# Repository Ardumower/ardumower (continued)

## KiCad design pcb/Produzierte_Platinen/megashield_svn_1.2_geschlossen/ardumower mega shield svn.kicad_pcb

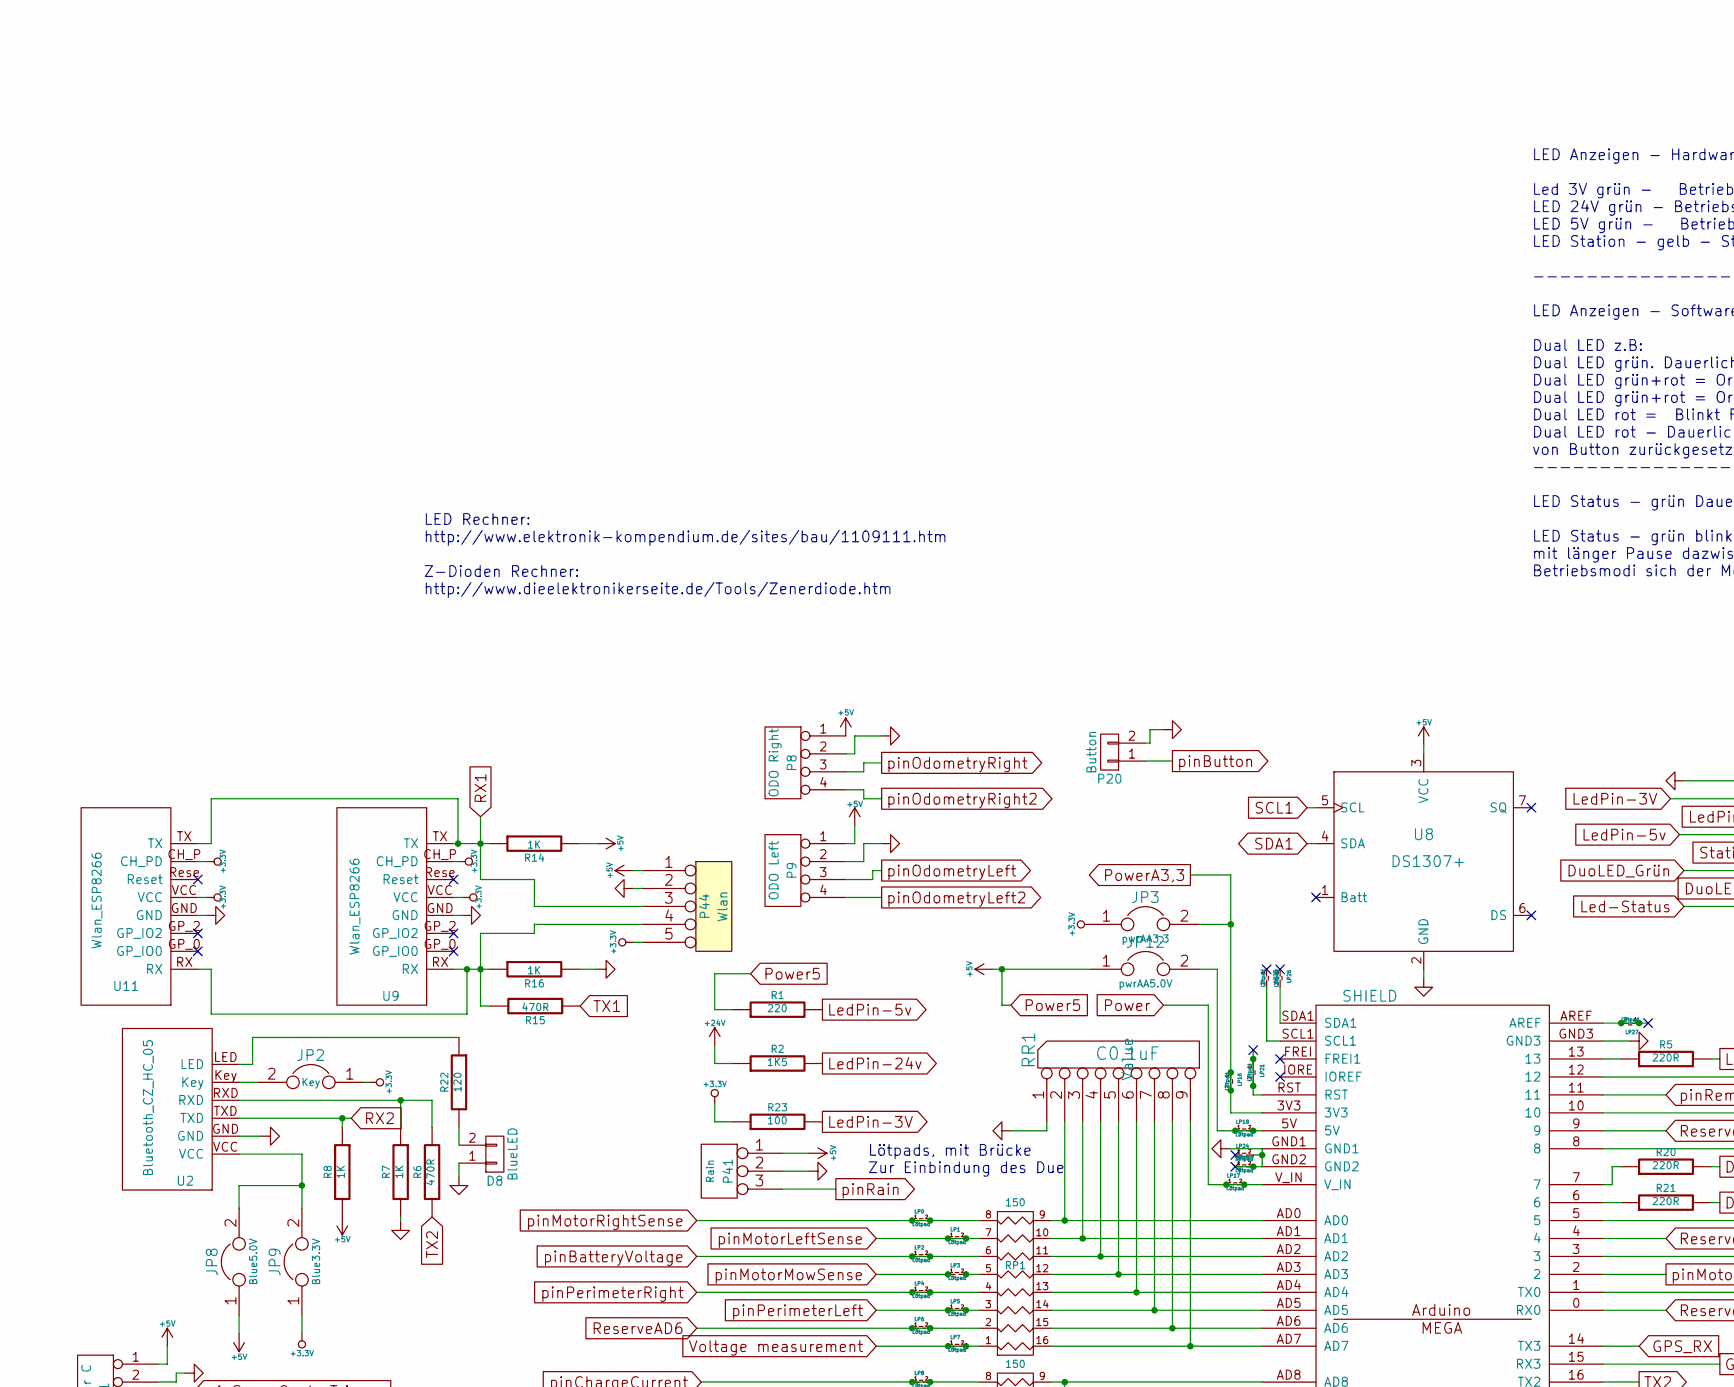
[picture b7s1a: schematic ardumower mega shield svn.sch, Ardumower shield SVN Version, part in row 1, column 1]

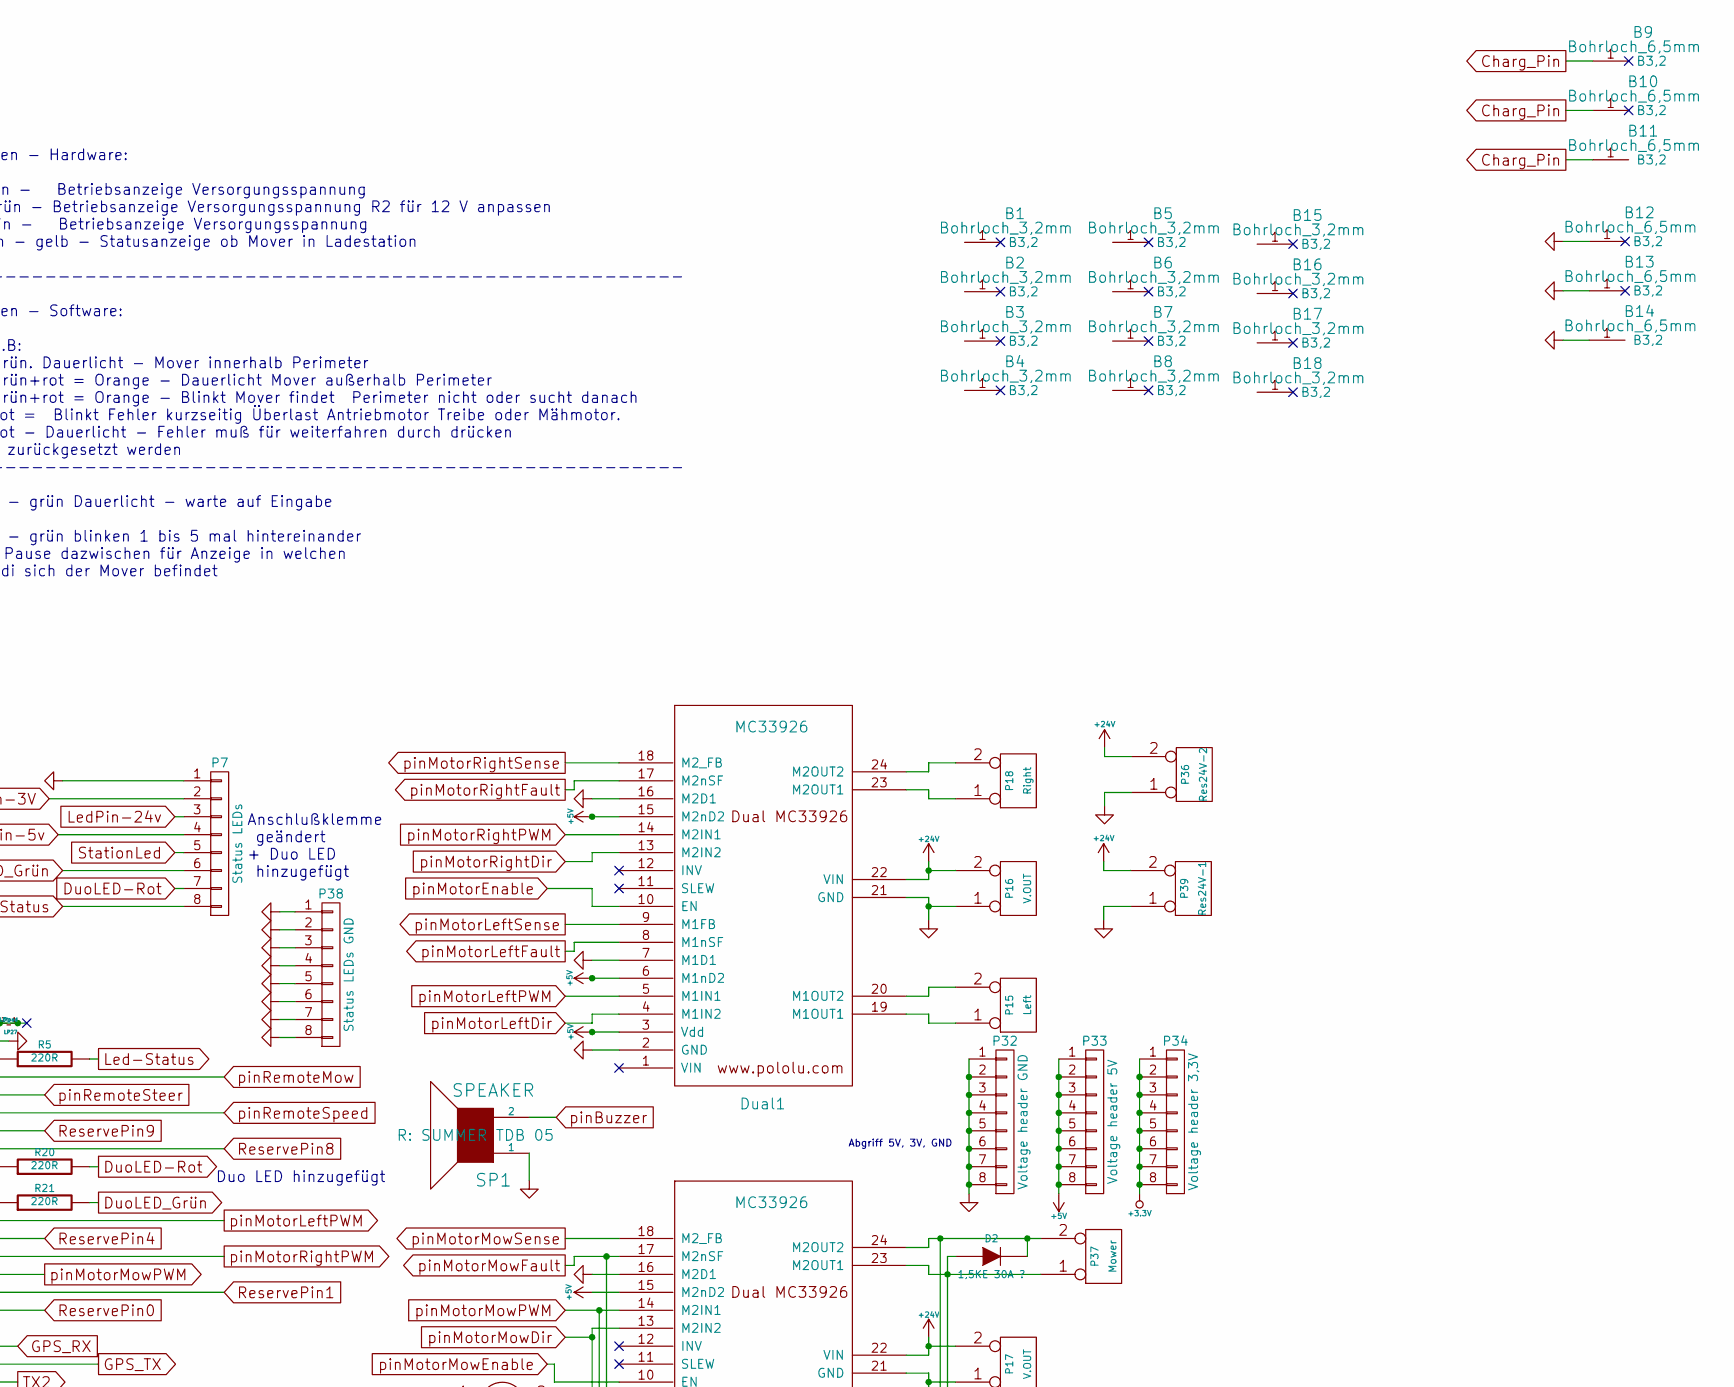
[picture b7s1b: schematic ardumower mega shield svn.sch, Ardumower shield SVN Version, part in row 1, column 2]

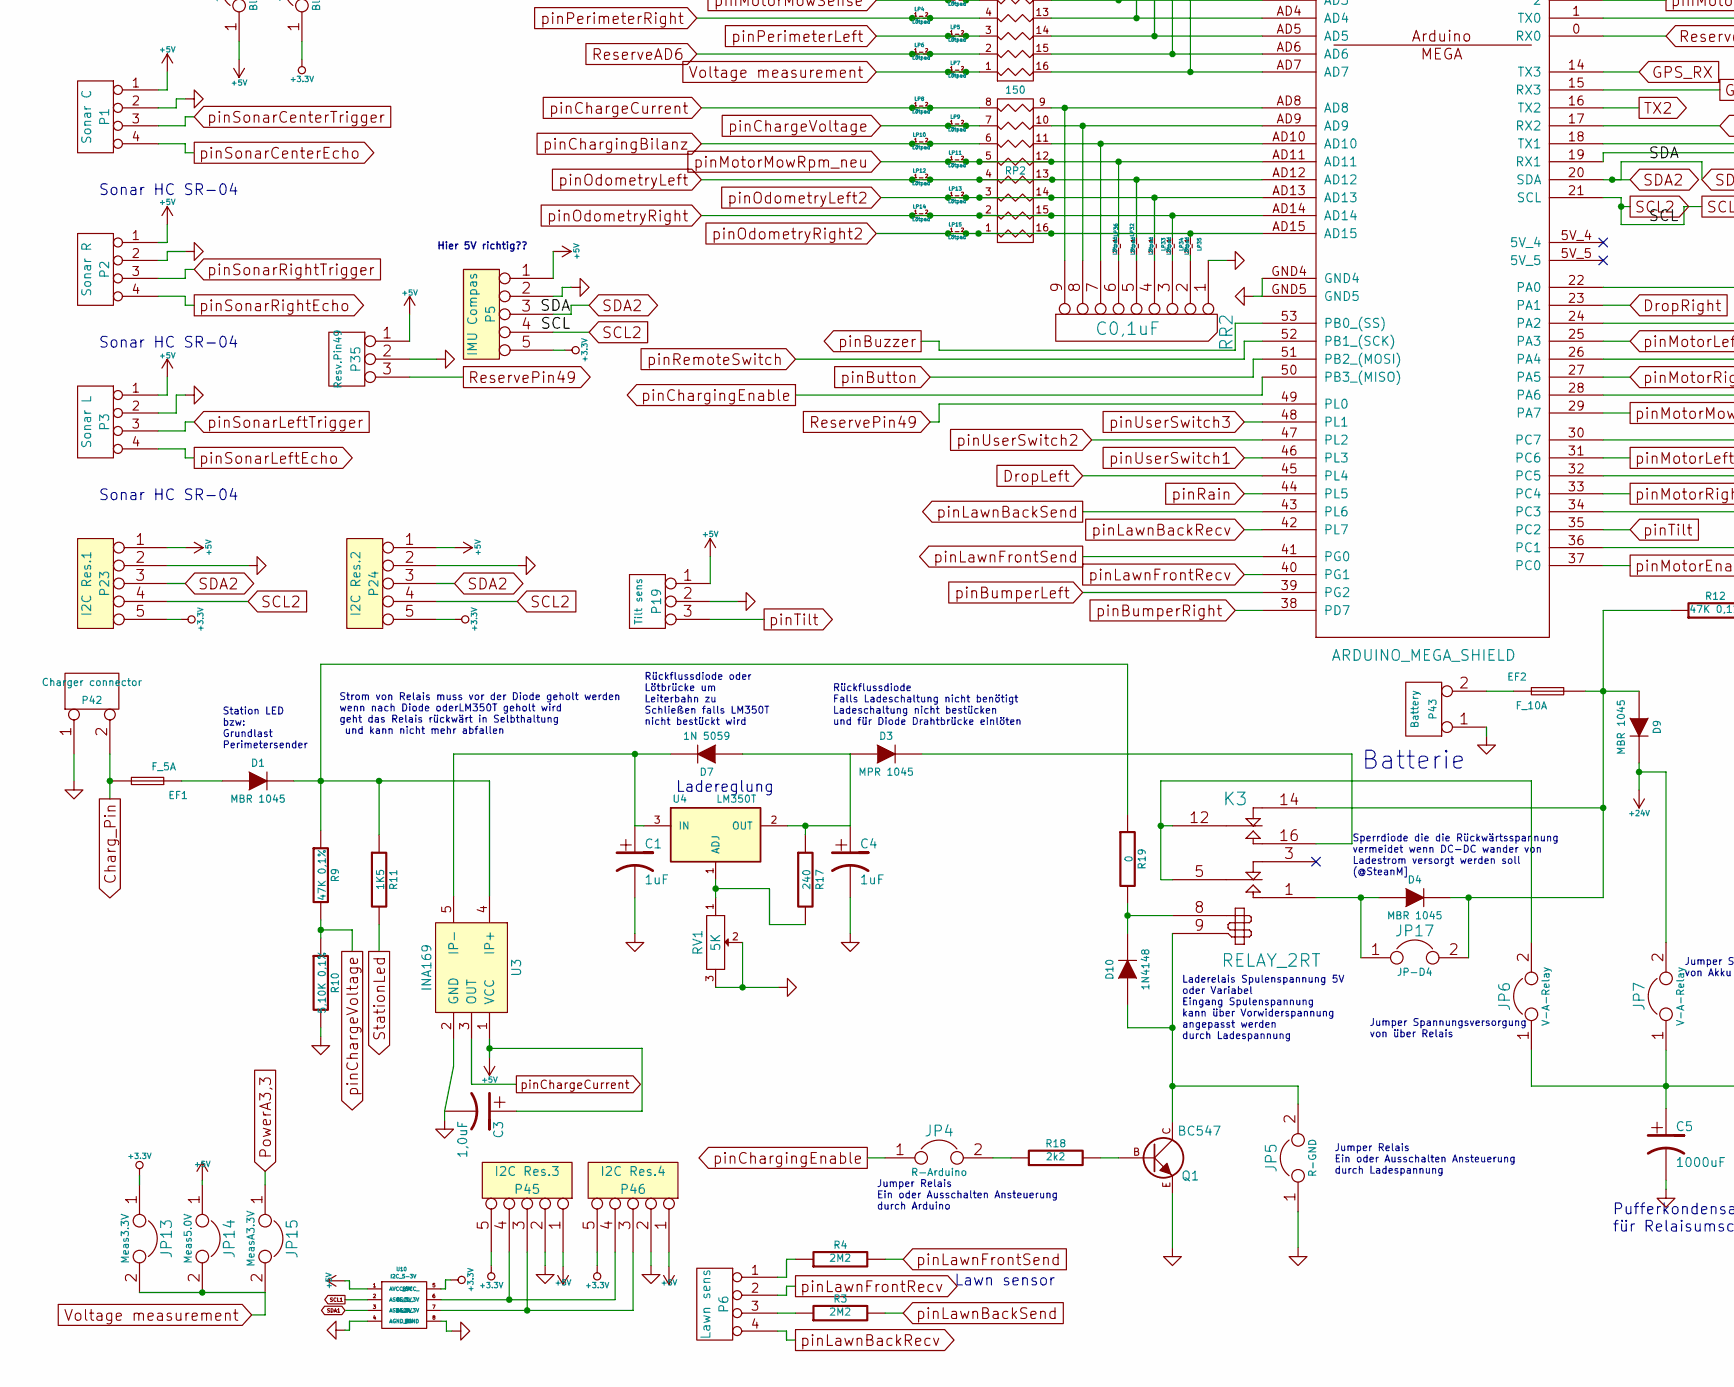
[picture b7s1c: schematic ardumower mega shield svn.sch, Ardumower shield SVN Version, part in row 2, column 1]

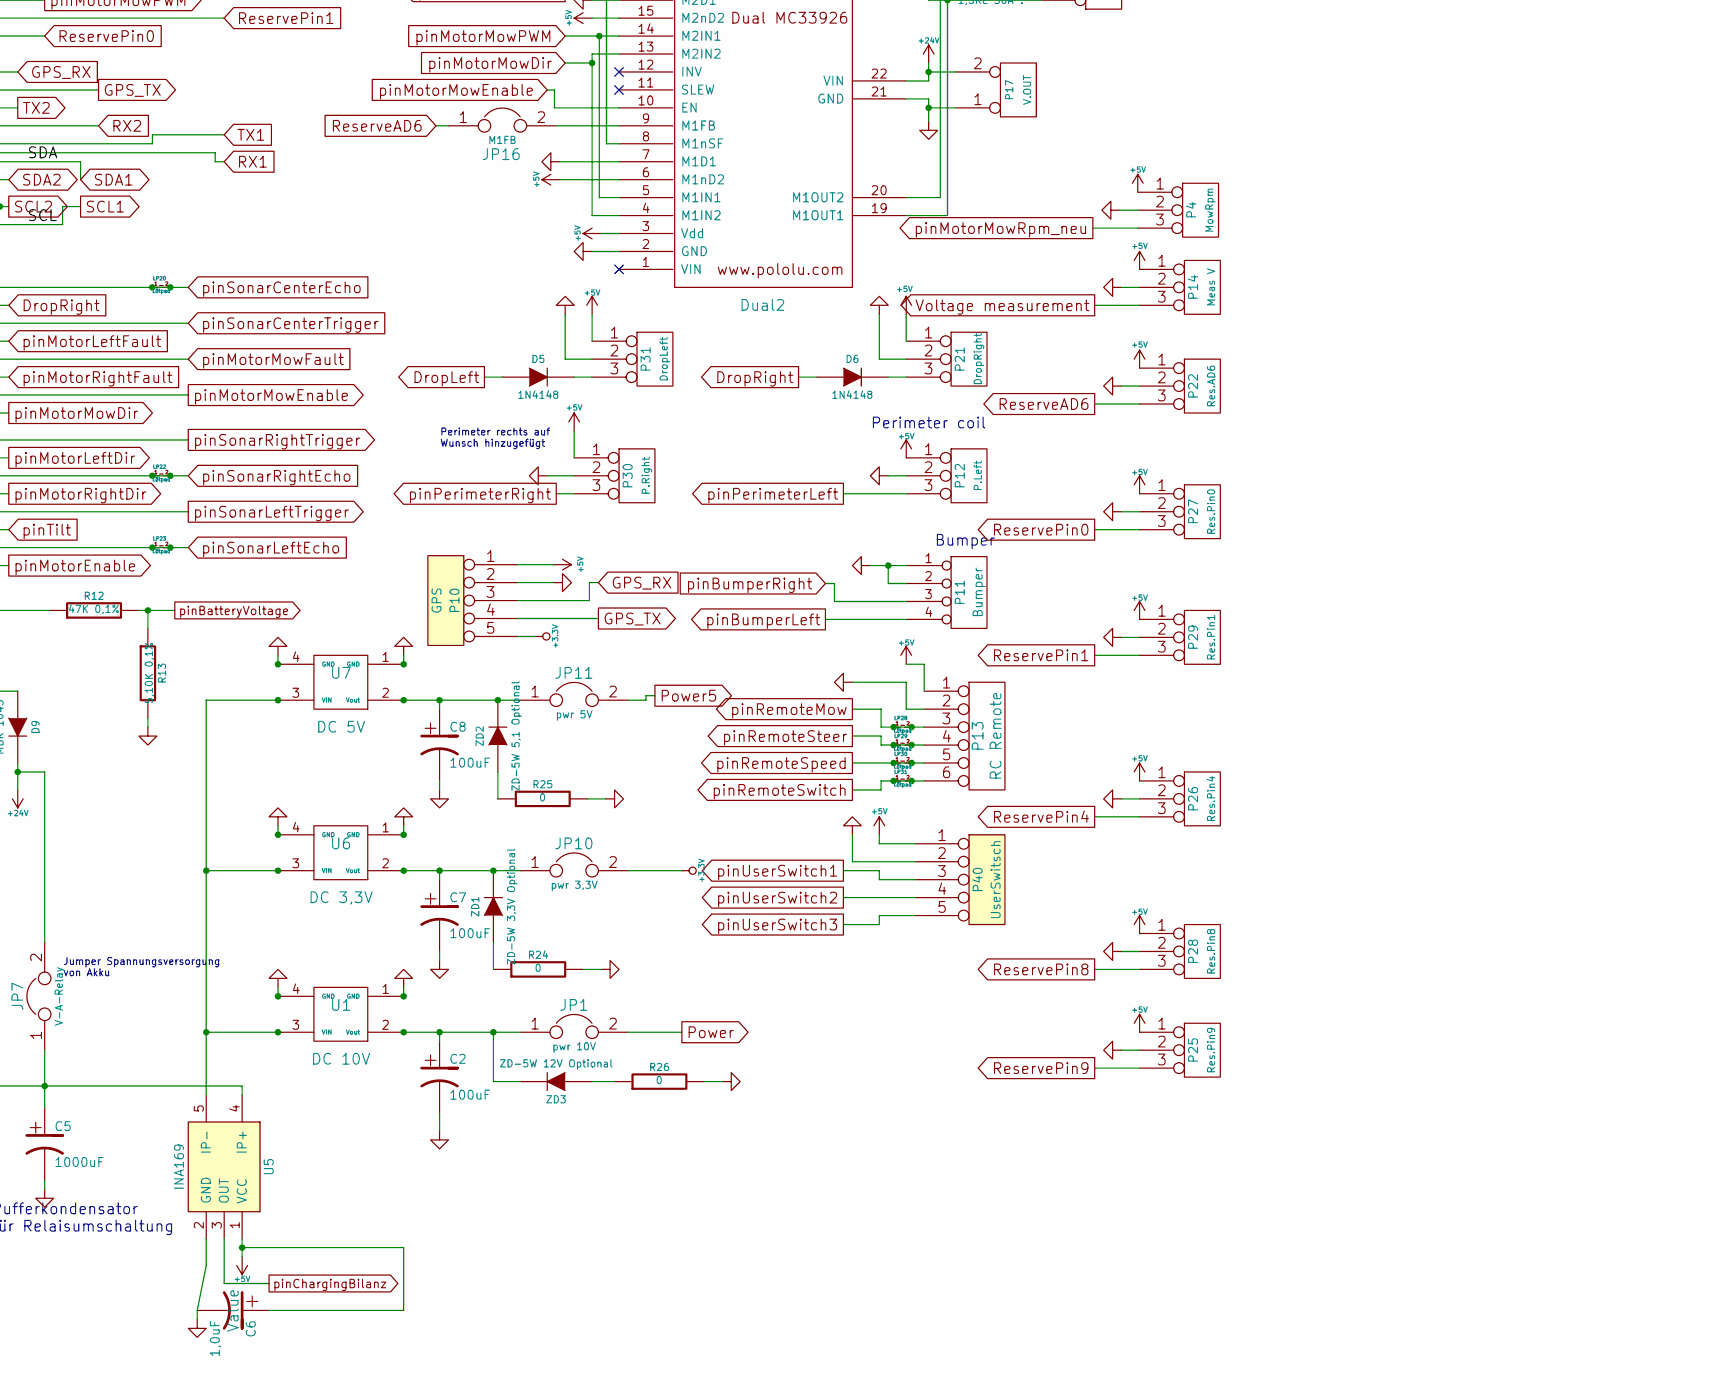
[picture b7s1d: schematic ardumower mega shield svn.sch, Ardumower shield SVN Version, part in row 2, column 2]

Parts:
B1, B2, B3, B4, B5, B6, B7, B8, B15, B16, B17, B18: Bohrloch_3,2mm
B9, B10, B11, B12, B13, B14: Bohrloch_6,5mm
C1, C4: 1uF; Elko_vert_11.2x6.3mm_RM2.5_RM5.0
C2, C7, C8: 100uF; Elko_vert_11.2x6.3mm_RM2.5_RM5.0
C3, C6: 1,0uF; Elko_vert_11.2x6.3mm_RM2.5_RM5.0
C5: 1000uF; Elko_vert_31.5x16mm_RM7.5
D1, D4: MBR 1045; MBR1045
D2: 1,5KE 30A ?; Diode_ligend_RM10
D3: MPR 1045; MBR1045
D5, D6, D10: 1N4148; Diode_ligend_RM10
D7: 1N 5059; Diode_ligend_RM10
D8: BlueLED; Diode_LED_5mm_round_vertical
D9: MBR 1045; MBR1045_liegend
Dual1, Dual2: MC33926; MC_33926_31polig_mit_Bohrloch_neue_Masse
EF1: F_5A; Fuseholder_Reichelt_PL112000
EF2: F_10A; Fuseholder_Reichelt_PL112000
JP1: pwr 10V; Pin_Header_Straight_1x02
JP2: Key; Pin_Header_Straight_1x02
JP3: pwrAA3,3; Pin_Header_Straight_1x02
JP4: R-Arduino; Pin_Header_Straight_1x02
JP5: R-GND; Pin_Header_Straight_1x02
JP6, JP7: V-A-Relay; Pin_Header_Straight_1x02
JP8: Blue5.0V; Pin_Header_Straight_1x02
JP9: Blue3.3V; Pin_Header_Straight_1x02
JP10: pwr 3,3V; Pin_Header_Straight_1x02
JP11: pwr 5V; Pin_Header_Straight_1x02
JP12: pwrAA5.0V; Pin_Header_Straight_1x02
JP13: Meas3.3V; Pin_Header_Straight_1x02
JP14: Meas5.0V; Pin_Header_Straight_1x02
JP15: MeasA3.3V; Pin_Header_Straight_1x02
JP16: M1FB; Pin_Header_Straight_1x02
JP17: JP-D4; Pin_Header_Straight_1x02
K3: RELAY_2RT; Relais_DPDT_Schrack-RT2_RM5mm_3D_Kontaktbelegung_geändert_F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
LP0, LP1, LP2, LP3, LP4, LP5, LP6, LP7, LP8, LP9, LP10, LP11, LP12, LP13, LP14, LP15, LP16, LP17, LP18, LP19, LP20, LP21, LP22, LP23, LP24, LP25, LP26, LP27, LP28, LP29, LP30, LP31: Lötpad; Lötpad_1x02
LP32, LP33, LP34, LP35, LP36: Lötpad; Lötpad0,508_CU
P1: Sonar C; Pin_Header_Straight_1x04
P2: Sonar R; Pin_Header_Straight_1x04
P3: Sonar L; Pin_Header_Straight_1x04
P4: MowRpm; Pin_Header_Straight_1x03
P5: IMU Compas; Pin_Header_Straight_1x05
P6: Lawn sens; Pin_Header_Straight_1x04
P7: Status LEDs; Pin_Header_Straight_1x08
P8: ODO Right; Pin_Header_Straight_1x04
P9: ODO Left; Pin_Header_Straight_1x04
P10: GPS; Pin_Header_Straight_1x05
P11: Bumper; Pin_Header_Straight_1x04
P12: P.Left; Pin_Header_Straight_1x03
P13: RC Remote; Pin_Header_Straight_1x06
P14: Meas V; Pin_Header_Straight_1x03
P15: Left; Anschlussklemme_2P_RM5,08
P16, P17: V.OUT; Anschlussklemme_2P_RM5,08
P18: Right; Anschlussklemme_2P_RM5,08
P19: Tilt sens; Pin_Header_Straight_1x03
P20: Button; Pin_Header_Straight_1x02
P21: DropRight; Pin_Header_Straight_1x03
P22: Res.AD6; Pin_Header_Straight_1x03
P23: I2C Res.1; Pin_Header_Straight_1x05
P24: I2C Res.2; Pin_Header_Straight_1x05
P25: Res.Pin9; Pin_Header_Straight_1x03
P26: Res.Pin4; Pin_Header_Straight_1x03
P27: Res.Pin0; Pin_Header_Straight_1x03
P28: Res.Pin8; Pin_Header_Straight_1x03
P29: Res.Pin1; Pin_Header_Straight_1x03
P30: P.Right; Pin_Header_Straight_1x03
P31: DropLeft; Pin_Header_Straight_1x03
P32: Voltage header GND; Pin_Header_Straight_1x08
P33: Voltage header 5V; Pin_Header_Straight_1x08
P34: Voltage header 3,3V; Pin_Header_Straight_1x08
P35: Resv.Pin49; Pin_Header_Straight_1x03
P36: Res24V-2; Anschlussklemme_2P_RM5,08
P37: Mower; Anschlussklemme_RM5,08-RM7,62
P38: Status LEDs GND; Pin_Header_Straight_1x08
P39: Res24V-1; Anschlussklemme_2P_RM5,08
P40: UserSwitsch; Pin_Header_Straight_1x05
P41: Rain; Pin_Header_Straight_1x03
P42: Charger connector; Anschlussklemme_RM5,08-RM7,62
P43: Battery; Anschlussklemme_RM5,08-RM7,62
P44: Wlan; Pin_Header_Straight_1x05
P45: I2C Res.3; Pin_Header_Straight_1x05
P46: I2C Res.4; Pin_Header_Straight_1x05
Q1: BC547; TO92-EBC
R1: 220; Resistor_Horizontal_RM15mm
R2, R11: 1K5; Resistor_Horizontal_RM10mm
R3, R4: 2M2; Resistor_Horizontal_RM10mm
R5, R20, R21: 220R; Resistor_Horizontal_RM15mm
R6, R15: 470R; Resistor_Horizontal_RM15mm
R7, R8, R14, R16: 1K; Resistor_Horizontal_RM15mm
R9: 47K 0,1%; Resistor_Horizontal_RM10mm
R10: 5,10K 0,1%; Resistor_Horizontal_RM10mm
R12: 47K 0,1%; Resistor_Horizontal_RM15mm
R13: 5,10K 0,1%; Resistor_Horizontal_RM15mm
R17: 240; Resistor_Horizontal_RM15mm
R18: 2k2; Resistor_Horizontal_RM10mm
R19: 0; Resistor_Horizontal_RM10mm
R22: 120; Resistor_Horizontal_RM15mm
R23: 100; Resistor_Horizontal_RM15mm
R24, R25, R26: 0; Resistor_Horizontal_RM15mm
RP1, RP2: 150; DIP-16__300
RR1, RR2: C0,1uF; Kondensatorenleiste_8er_9pin_3D
RV1: 5K; Potentiometer_VishaySpectrol-Econtrim-Type36T_3D
SHIELD1: ARDUINO_MEGA_SHIELD; ARDUINO_MEGA_SHIELD_DUO_3D
SP1: SPEAKER; Buzzer_12x9.5RM7.6_RM5.0
U1: DC 10V; DC_DC_DSN2596_mit_Bohrloch_doppelte_Lochreihe
U2: Bluetooth_CZ_HC_05; Bluetooth_Buchse_Platz
U3, U5: INA169
U4: LM350T; LM350T_3D_muss_noch_auf_Masse_geprüft_werden
U6: DC 3,3V; DC_DC_DSN2596_mit_Bohrloch_doppelte_Lochreihe
U7: DC 5V; DC_DC_DSN2596_mit_Bohrloch_doppelte_Lochreihe
U8: DS1307+; Tiny_RTC_DS1307_geändert_mit_Bohrloch_4Lochreihen
U9, U11: Wlan_ESP8266; Wlan_ESP8266_3D
U10: I2C_5-3V
ZD1: ZD-5W 3,3V Optional; Diode_ligend_RM10
ZD2: ZD-5W 5,1 Optional; Diode_ligend_RM10
ZD3: ZD-5W 12V Optional; Diode_ligend_RM10

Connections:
+3.3V: JP2.1, JP3.1, JP9.1, JP10.2, JP13.1, P5.5, P10.5, P23.5, P24.5, P34.1, P34.2, P34.3, P34.4, P34.5, P34.6, P34.7, P34.8, P44.5, P45.5, P46.5, R23.1, U9.CH_P (CH_PD), U9.VCC, U10.5 (BVCC_), U11.CH_P (CH_PD), U11.VCC
+24V: D9.2 (K), Dual1.22 (VIN), Dual2.22 (VIN), JP7.2, P16.2 (PM), P17.2 (PM), P36.2 (PM), P39.2 (PM), R2.1
Charg_Pin: B9.1, B10.1, B11.1, EF1.1, P42.2 (PM)
DropLeft: D5.1 (A), SHIELD1.45 (PL4)
DropRight: D6.1 (A), SHIELD1.23 (PA1)
DuoLED-Rot: P7.7, R20.2
DuoLED_Grün: P7.6, R21.2
GND: B12.1, B13.1, B14.1, C1.2, C2.2, C3.2, C4.2, C5.2, C6.2, C7.2, C8.2, D8.1, Dual1.2 (GND), Dual1.7 (M1D1), Dual1.16 (M2D1), Dual1.21 (GND), Dual2.2 (GND), Dual2.7 (M1D1), Dual2.16 (M2D1), Dual2.21 (GND), JP5.1, LP19.1, LP19.2, LP24.1, LP24.2, P1.2, P2.2, P3.2, P4.2 (PM), P5.2, P7.1, P8.2, P9.2, P10.2, P11.1, P11.2, P12.2 (PM), P13.2, P14.2 (PM), P16.1, P17.1, P19.2 (PM), P20.2, P21.2 (PM), P22.2 (PM), P23.2, P24.2, P25.2 (PM), P26.2 (PM), P27.2 (PM), P28.2 (PM), P29.2 (PM), P30.2 (PM), P31.2 (PM), P32.1, P32.2, P32.3, P32.4, P32.5, P32.6, P32.7, P32.8, P35.2 (PM), P36.1, P38.1, P38.2, P38.3, P38.4, P38.5, P38.6, P38.7, P38.8, P39.1, P40.2, P41.2 (PM), P42.1, P43.1, P44.2, P45.2, P46.2, Q1.E, R7.2, R10.2, R13.2, R16.2, R24.2, R25.2, R26.2, RR1.1 (COM), RR2.1 (COM), RV1.2, RV1.3, SHIELD1.GND1, SHIELD1.GND2, SHIELD1.GND3, SHIELD1.GND4, SHIELD1.GND5, SP1.1, U1.1 (GND), U1.4 (GND), U2.GND, U3.2 (GND), U5.2 (GND), U6.1 (GND), U6.4 (GND), U7.1 (GND), U7.4 (GND), U8.2 (GND), U9.GND, U10.4 (AGND_5V), U10.8 (BGND), U11.GND
GPS_RX: P10.3, SHIELD1.14 (TX3)
GPS_TX: P10.4, SHIELD1.15 (RX3)
Led-Status: P7.8, R5.2
LedPin-3V: P7.2, R23.2
LedPin-5v: P7.4, R1.2
LedPin-24v: P7.3, R2.2
unnamed: C1.1, D7.2 (K), U3.5 (IP-), U4.3 (IN)
unnamed: C2.1, JP1.1, U1.2 (Vout), ZD3.2 (K)
unnamed: C4.1, D3.1 (A), D7.1 (A), R17.1, U4.2 (OUT)
unnamed: C5.1, JP6.1, JP7.1, U5.4 (IP+)
unnamed: C7.1, JP10.1, U6.2 (Vout), ZD1.2 (K)
unnamed: C8.1, JP11.1, U7.2 (Vout), ZD2.2 (K)
unnamed: D1.1 (A), EF1.2
unnamed: D1.2 (K), R9.1, R11.1, R19.1, U3.4 (IP+)
unnamed: D2.1 (A), Dual2.19 (M1OUT1), Dual2.23 (M2OUT1), P37.1
unnamed: D2.2 (K), Dual2.20 (M1OUT2), Dual2.24 (M2OUT2), P37.2 (PM)
unnamed: D3.2 (K), K3.16 (T2)
unnamed: D4.1 (A), JP17.1, K3.1 (T1)
unnamed: D4.2 (K), D9.1 (A), EF2.1, JP17.2, K3.14 (R2), R12.1
unnamed: D5.2 (K), P31.3
unnamed: D6.2 (K), P21.3
unnamed: D8.2, R22.2
unnamed: D10.1 (A), JP5.2, K3.9, Q1.C
unnamed: D10.2 (K), K3.8, R19.2
unnamed: Dual1.19 (M1OUT1), P15.1
unnamed: Dual1.20 (M1OUT2), P15.2 (PM)
unnamed: Dual1.23 (M2OUT1), P18.1
unnamed: Dual1.24 (M2OUT2), P18.2 (PM)
unnamed: Dual2.9 (M1FB), JP16.2
unnamed: EF2.2, P43.2 (PM)
unnamed: JP2.2, U2.Key
unnamed: JP4.2, R18.1
unnamed: JP6.2, K3.5 (C1), K3.12 (C2)
unnamed: JP8.2, JP9.2, U2.VCC
unnamed: JP12.2, LP18.1, LP18.2, SHIELD1.5V
unnamed: LP3.2, RP1.5
unnamed: LP21.1, LP21.2, SHIELD1.RST
unnamed: LP25.2, SHIELD1.SCL1
unnamed: LP26.2, SHIELD1.SDA1
unnamed: LP27.1, LP27.2, SHIELD1.AREF
unnamed: LP32.2, RR2.5
unnamed: LP33.2, RR2.4
unnamed: LP34.2, RR2.3
unnamed: LP35.2, RR2.2
unnamed: LP36.2, RR2.6
unnamed: P6.1, R4.1
unnamed: P6.3, R3.1
unnamed: P44.4, R15.2, R16.1, U9.RX, U11.RX
unnamed: P45.3, P46.3, U10.7 (BSDA_3V)
unnamed: P45.4, P46.4, U10.6 (BSCL_3V)
unnamed: Q1.B, R18.2
unnamed: R5.1, SHIELD1.13
unnamed: R6.2, R7.1, U2.RXD
unnamed: R17.2, RV1.1, U4.1 (ADJ)
unnamed: R20.1, SHIELD1.7
unnamed: R21.1, SHIELD1.6
unnamed: R22.1, U2.LED
unnamed: R24.1, ZD1.1 (A)
unnamed: R25.1, ZD2.1 (A)
unnamed: R26.1, ZD3.1 (A)
unnamed: RP1.9 (R8), RR1.2, SHIELD1.AD0
unnamed: RP1.10 (R7), RR1.3, SHIELD1.AD1
unnamed: RP1.11 (R6), RR1.4, SHIELD1.AD2
unnamed: RP1.12 (R5), RR1.5, SHIELD1.AD3
unnamed: RP1.13 (R4), RR1.6, SHIELD1.AD4
unnamed: RP1.14 (R3), RR1.7, SHIELD1.AD5
unnamed: RP1.15 (R2), RR1.8, SHIELD1.AD6
unnamed: RP1.16 (R1), RR1.9, SHIELD1.AD7
unnamed: RP2.9 (R8), RR2.9, SHIELD1.AD8
unnamed: RP2.10 (R7), RR2.8, SHIELD1.AD9
unnamed: RP2.11 (R6), RR2.7, SHIELD1.AD10
unnamed: U1.3 (VIN), U5.5 (IP-), U6.3 (VIN), U7.3 (VIN)
Power: JP1.2, LP17.1, LP17.2, SHIELD1.V_IN
Power5: C3.1, C6.1, Dual1.3 (Vdd), Dual1.6 (M1nD2), Dual1.15 (M2nD2), Dual2.3 (Vdd), Dual2.6 (M1nD2), Dual2.15 (M2nD2), JP8.1, JP11.2, JP12.1, JP14.1, P1.1, P2.1, P3.1, P4.1, P5.1, P8.1, P9.1, P10.1, P12.1, P13.1, P14.1, P19.1, P21.1, P22.1, P23.1, P24.1, P25.1, P26.1, P27.1, P28.1, P29.1, P30.1, P31.1, P33.1, P33.2, P33.3, P33.4, P33.5, P33.6, P33.7, P33.8, P35.1, P40.1, P41.1, P44.1, P45.1, P46.1, R1.1, R8.2, R14.2, U3.1 (VCC), U5.1 (VCC), U8.3 (VCC), U10.1 (AVCC_5V)
PowerA3,3: JP3.2, JP15.1, LP16.1, LP16.2, SHIELD1.3V3
RX1: P44.3, R14.1, SHIELD1.19 (RX1), U9.TX, U11.TX
RX2: R8.1, SHIELD1.17 (RX2), U2.TXD
ReserveAD6: JP16.1, LP6.1, LP6.2, P22.3, RP1.2
ReservePin0: P27.3, SHIELD1.0 (RX0)
ReservePin1: P29.3, SHIELD1.1 (TX0)
ReservePin4: P26.3, SHIELD1.4
ReservePin8: P28.3, SHIELD1.8
ReservePin9: P25.3, SHIELD1.9
ReservePin49: P35.3, SHIELD1.49 (PL0)
SCL2: P5.4, P23.4, P24.4, SHIELD1.21 (SCL), U8.5 (SCL), U10.2 (ASCL_5V)
SDA2: P5.3, P23.3, P24.3, SHIELD1.20 (SDA), U8.4 (SDA), U10.3 (ASDA_5V)
StationLed: P7.5, R11.2
TX1: R15.1, SHIELD1.18 (TX1)
TX2: R6.1, SHIELD1.16 (TX2)
Voltage measurement: JP13.2, JP14.2, JP15.2, LP7.1, LP7.2, P14.3, RP1.1
pinBatteryVoltage: LP2.1, LP2.2, R12.2, R13.1, RP1.6
pinBumperLeft: P11.4, SHIELD1.39 (PG2)
pinBumperRight: P11.3, SHIELD1.38 (PD7)
pinButton: P20.1, SHIELD1.51 (PB2_(MOSI))
pinBuzzer: SHIELD1.53 (PB0_(SS)), SP1.2
pinChargeCurrent: LP8.1, LP8.2, RP2.8, U3.3 (OUT)
pinChargeVoltage: LP9.1, LP9.2, R9.2, R10.1, RP2.7
pinChargingBilanz: LP10.1, LP10.2, RP2.6, U5.3 (OUT)
pinChargingEnable: JP4.1, SHIELD1.50 (PB3_(MISO))
pinLawnBackRecv: P6.4, SHIELD1.42 (PL7)
pinLawnBackSend: R3.2, SHIELD1.43 (PL6)
pinLawnFrontRecv: P6.2, SHIELD1.40 (PG1)
pinLawnFrontSend: R4.2, SHIELD1.41 (PG0)
pinMotorEnable: Dual1.10 (EN), SHIELD1.37 (PC0)
pinMotorLeftDir: Dual1.4 (M1IN2), SHIELD1.31 (PC6)
pinMotorLeftFault: Dual1.8 (M1nSF), SHIELD1.25 (PA3)
pinMotorLeftPWM: Dual1.5 (M1IN1), SHIELD1.5
pinMotorLeftSense: Dual1.9 (M1FB), LP1.1, LP1.2, RP1.7
pinMotorMowDir: Dual2.4 (M1IN2), Dual2.13 (M2IN2), SHIELD1.29 (PA7)
pinMotorMowEnable: Dual2.10 (EN), SHIELD1.28 (PA6)
pinMotorMowFault: Dual2.8 (M1nSF), Dual2.17 (M2nSF), SHIELD1.26 (PA4)
pinMotorMowPWM: Dual2.5 (M1IN1), Dual2.14 (M2IN1), SHIELD1.2
pinMotorMowRpm_neu: LP11.1, LP11.2, LP36.1, P4.3, RP2.5, RP2.12 (R5), SHIELD1.AD11
pinMotorMowSense: Dual2.18 (M2_FB), LP3.1
pinMotorRightDir: Dual1.13 (M2IN2), SHIELD1.33 (PC4)
pinMotorRightFault: Dual1.17 (M2nSF), SHIELD1.27 (PA5)
pinMotorRightPWM: Dual1.14 (M2IN1), SHIELD1.3
pinMotorRightSense: Dual1.18 (M2_FB), LP0.1, LP0.2, RP1.8
pinOdometryLeft: LP12.1, LP12.2, LP32.1, P9.3, RP2.4, RP2.13 (R4), SHIELD1.AD12
pinOdometryLeft2: LP13.1, LP13.2, LP33.1, P9.4, RP2.3, RP2.14 (R3), SHIELD1.AD13
pinOdometryRight: LP14.1, LP14.2, LP34.1, P8.3, RP2.2, RP2.15 (R2), SHIELD1.AD14
pinOdometryRight2: LP15.1, LP15.2, LP35.1, P8.4, RP2.1, RP2.16 (R1), SHIELD1.AD15
pinPerimeterLeft: LP5.1, LP5.2, P12.3, RP1.3
pinPerimeterRight: LP4.1, LP4.2, P30.3, RP1.4
pinRain: P41.3, SHIELD1.44 (PL5)
pinRemoteMow: LP28.1, LP28.2, P13.3, SHIELD1.12
pinRemoteSpeed: LP30.1, LP30.2, P13.5, SHIELD1.10
pinRemoteSteer: LP29.1, LP29.2, P13.4, SHIELD1.11
pinRemoteSwitch: LP31.1, LP31.2, P13.6, SHIELD1.52 (PB1_(SCK))
pinSonarCenterEcho: LP20.1, LP20.2, P1.4, SHIELD1.22 (PA0)
pinSonarCenterTrigger: P1.3, SHIELD1.24 (PA2)
pinSonarLeftEcho: LP23.1, LP23.2, P3.4, SHIELD1.36 (PC1)
pinSonarLeftTrigger: P3.3, SHIELD1.34 (PC3)
pinSonarRightEcho: LP22.1, LP22.2, P2.4, SHIELD1.32 (PC5)
pinSonarRightTrigger: P2.3, SHIELD1.30 (PC7)
pinTilt: P19.3, SHIELD1.35 (PC2)
pinUserSwitch1: P40.3, SHIELD1.46 (PL3)
pinUserSwitch2: P40.4, SHIELD1.47 (PL2)
pinUserSwitch3: P40.5, SHIELD1.48 (PL1)

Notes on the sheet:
Sonar HC SR-04
Perimeter coil
Lawn sensor
Bumper
Batterie
Pufferkondensator für Relaisumschaltung
Jumper Spannungsversorgung von Akku
Jumper Spannungsversorgung von über Relais
Jumper Relais Ein oder Ausschalten Ansteuerung durch Arduino
Jumper Relais Ein oder Ausschalten Ansteuerung durch Ladespannung
Laderelais Spulenspannung 5V oder Variabel Eingang Spulenspannung kann über Vorwiderspannung angepasst werden durch Ladespannung
Rückflussdiode Falls Ladeschaltung nicht benötigt Ladeschaltung nicht bestücken und für Diode Drahtbrücke einlöten
Anschlußklemme geändert + Duo LED hinzugefügt
Duo LED hinzugefügt
Station LED bzw: Grundlast Perimetersender
Strom von Relais muss vor der Diode geholt werden wenn nach Diode oderLM350T geholt wird geht das Relais rückwärt in Selbthaltung und kann nicht mehr abfallen
Hier 5V richtig??
Sperrdiode die die Rückwärtsspannung vermeidet wenn DC-DC wander von Ladestrom versorgt werden soll (@SteanM]
Rückflussdiode oder Lötbrücke um Leiterbahn zu Schließen falls LM350T nicht bestückt wird
Perimeter rechts auf Wunsch hinzugefügt
Abgriff 5V, 3V, GND
LED Anzeigen - Hardware: Led 3V grün - Betriebsanzeige Versorgungsspannung LED 24V grün - Betriebsanzeige Versorgungsspannung R2 für 12 V anpassen LED 5V grün - Betriebsanzeige Versorgungsspannung LED Station - gelb - Statusanzeige ob Mover in Ladestation -------------------------------------------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
LED Rechner: http://www.elektronik-kompendium.de/sites/bau/1109111.htm Z-Dioden Rechner: http://www.dieelektronikerseite.de/Tools/Zenerdiode.htm
Ladereglung
Lötpads, mit Brücke Zur Einbindung des Due

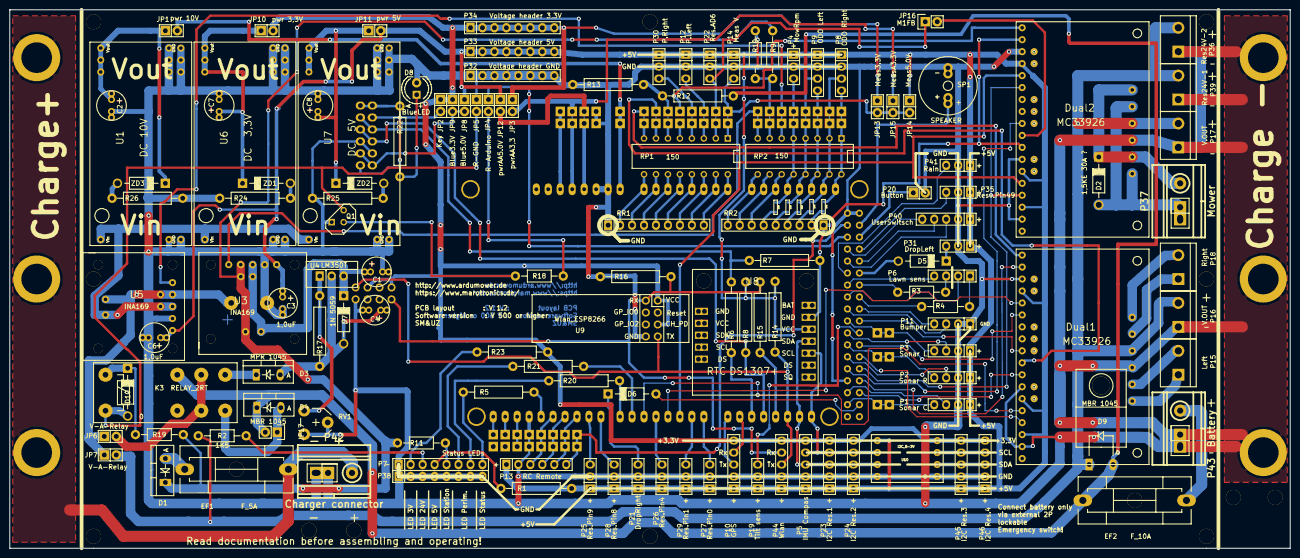
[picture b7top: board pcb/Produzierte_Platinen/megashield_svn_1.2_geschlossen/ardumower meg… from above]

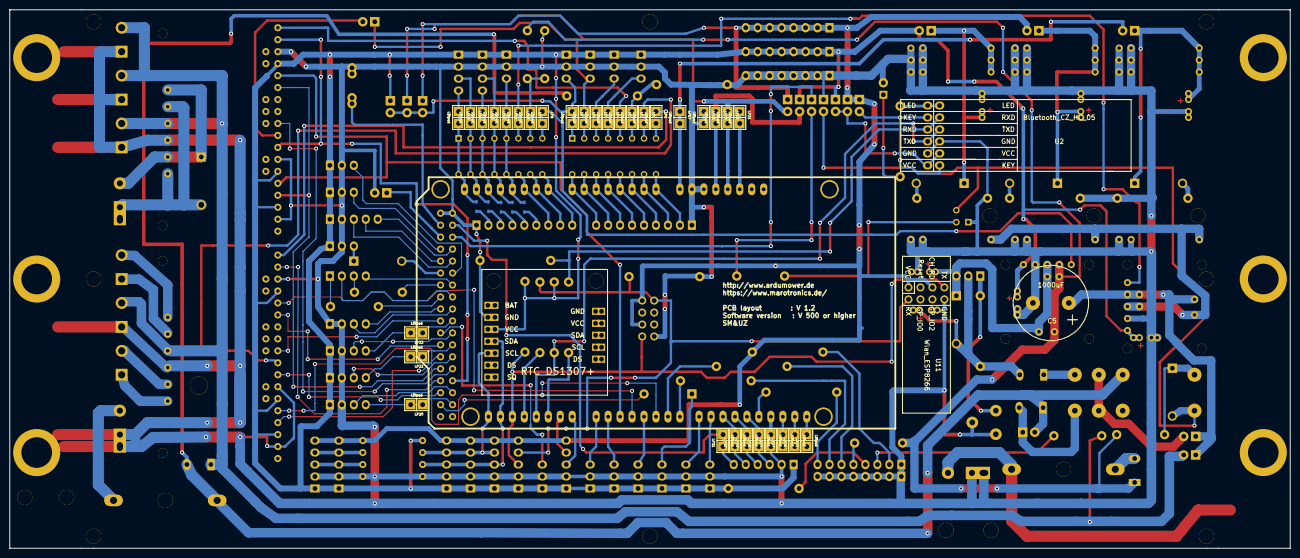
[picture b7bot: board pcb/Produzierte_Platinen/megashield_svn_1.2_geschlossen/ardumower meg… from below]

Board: 2 copper layers, 271.8 x 114.3 mm, 189 parts (36 on the bottom side), 147 nets.

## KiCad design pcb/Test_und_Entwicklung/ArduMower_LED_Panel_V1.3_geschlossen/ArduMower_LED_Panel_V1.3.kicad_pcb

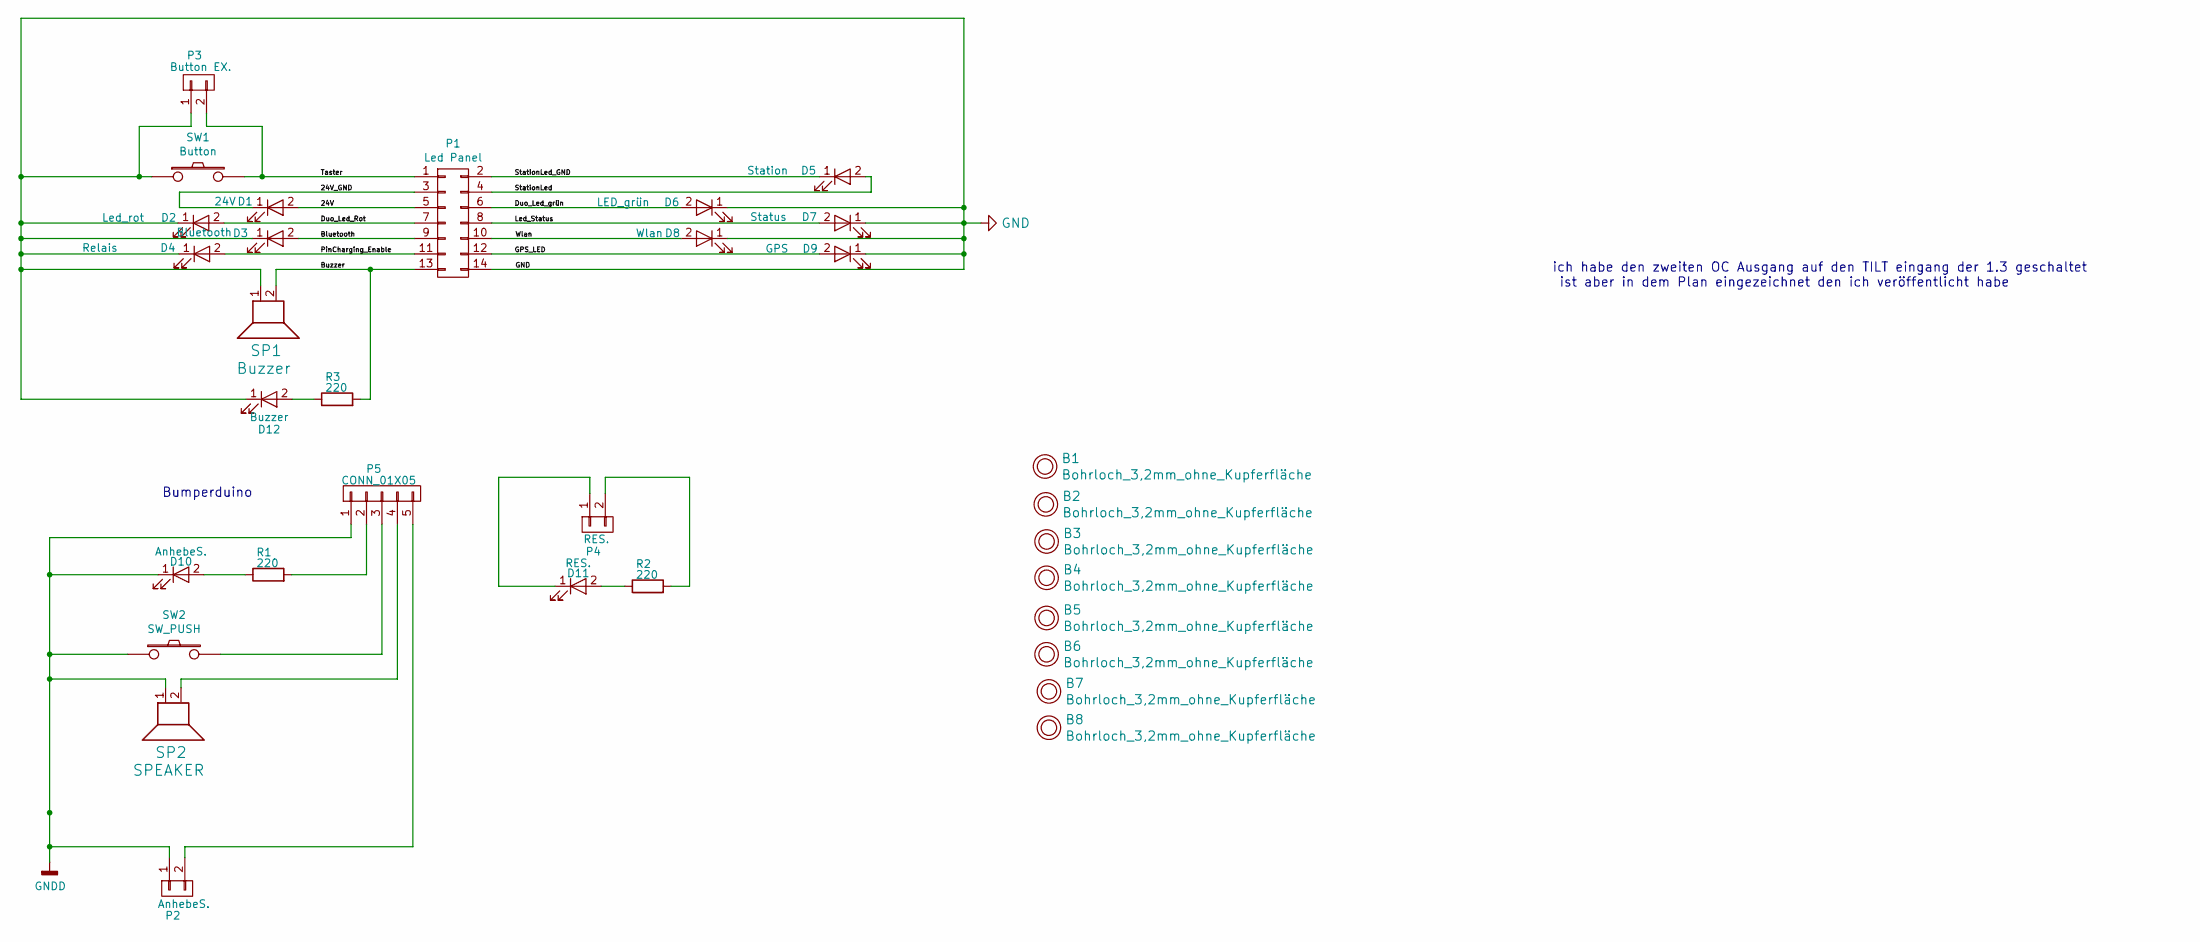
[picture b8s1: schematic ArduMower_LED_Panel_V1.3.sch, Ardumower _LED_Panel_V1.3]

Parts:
B1, B2, B3, B4, B5, B6, B7, B8: Bohrloch_3,2mm_ohne_Kupferfläche; Bohrloch_3,2mm
D1: 24V; LED_D5.0mm
D2: Led_rot; LED_D5.0mm
D3: Bluetooth; LED_D5.0mm
D4: Relais; LED_D5.0mm
D5: Station; LED_D5.0mm
D6: LED_grün; LED_D5.0mm
D7: Status; LED_D5.0mm
D8: Wlan; LED_D5.0mm
D9: GPS; LED_D5.0mm
D10: AnhebeS.; LED_D5.0mm
D11: RES.; LED_D5.0mm
D12: Buzzer; LED_D5.0mm
P1: Led Panel; Pin_Header_Angled_2x07_Pitch2.54mm
P2: AnhebeS.; Pin_Header_Angled_1x02_Pitch2.54mm
P3: Button EX.; Pin_Header_Angled_1x02_Pitch2.54mm
P4: RES.; Pin_Header_Angled_1x02_Pitch2.54mm
P5: CONN_01X05; JST_XH_S05B-XH-A_05x2.50mm_Angled
R1, R2, R3: 220; R_Axial_DIN0207_L6.3mm_D2.5mm_P10.16mm_Horizontal
SP1: Buzzer; Buzzer_12x9.5RM7.6_RM5.0
SP2: SPEAKER; Buzzer_12x9.5RM7.6_RM5.0
SW1: Button; SW_PUSH_6mm_h8.5mm
SW2: SW_PUSH; SW_PUSH_6mm_h8.5mm

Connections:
/24V: D1.2 (A), P1.5
/24V_GND: D1.1 (K), P1.3
/Bluetooth: D3.2 (A), P1.9
/Buzzer: P1.13, R3.2, SP1.2
/Duo_Led_Rot: D2.2 (A), P1.7
/Duo_Led_grün: D6.2 (A), P1.6
/GPS_LED: D9.2 (A), P1.12
/Led_Status: D7.2 (A), P1.8
/PinCharging_Enable: D4.2 (A), P1.11
/StationLed: D5.2 (A), P1.4
/StationLed_GND: D5.1 (K), P1.2
/Taster: P1.1, P3.2, SW1.2
/Wlan: D8.2 (A), P1.10
GND: D2.1 (K), D3.1 (K), D4.1 (K), D6.1 (K), D7.1 (K), D8.1 (K), D9.1 (K), D12.1 (K), P1.14, P3.1, SP1.1, SW1.1
GNDD: D10.1 (K), P2.1, P5.1, SP2.1, SW2.1
unnamed: D10.2 (A), R1.1
unnamed: D11.1 (K), P4.1
unnamed: D11.2 (A), R2.1
unnamed: D12.2 (A), R3.1
unnamed: P2.2, P5.5
unnamed: P4.2, R2.2
unnamed: P5.2, R1.2
unnamed: P5.3, SW2.2
unnamed: P5.4, SP2.2

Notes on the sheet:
Bumperduino
ich habe den zweiten OC Ausgang auf den TILT eingang der 1.3 geschaltet ist aber in dem Plan eingezeichnet den ich veröffentlicht habe
